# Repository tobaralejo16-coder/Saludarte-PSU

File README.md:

# Saludarte-PSU

### Sistema de asistencia y acompañamiento mediante aplicación Android y ESP32

**Saludarte_PSU** es un proyecto desarrollado en el contexto de PSU, que integra una aplicación móvil Android, un sistema embebido basado en ESP32 y un diseño de hardware electrónico para implementar funciones de asistencia, recordatorios y comunicación entre dispositivos.

El repositorio reúne el código fuente, los recursos multimedia y los archivos de diseño electrónico utilizados durante el desarrollo, montaje y pruebas del sistema.

## 1. Descripción del proyecto

Saludarte busca integrar herramientas de software y hardware en una solución tecnológica de apoyo a las actividades cotidianas.

El sistema integra:

- Una aplicación móvil Android para la interacción con el usuario.
- Un dispositivo basado en ESP32 para ejecutar las funciones del sistema embebido.
- Comunicación inalámbrica Bluetooth Low Energy (BLE) entre la aplicación y la ESP32.
- Recursos de audio para recordatorios, actividades y notificaciones.
- Hardware electrónico utilizado como referencia para el montaje, las conexiones y la soldadura de los componentes físicos del sistema.

## 2. Estructura del repositorio

```text
Saludarte-PSU/
│
├── App-Android/
│   └── Código fuente y recursos de la aplicación
│
├── Esp32/
│   └── Firmware, audios y configuración de ESP32
│
├── Hardware/
│   └── ESP32_Audio_3SPK/
│       ├── ESP32_Audio_3SPK.kicad_pro
│       ├── ESP32_Audio_3SPK.kicad_sch
│       ├── ESP32_Audio_3SPK.kicad_pcb
│       ├── Proyecto_Audio.pretty/
│       ├── models/
│       ├── vista/
│       └── Archivos complementarios
│
├── .gitignore
└── README.md
```

## 3. Aplicación Android

La aplicación está desarrollada en **Kotlin**, utilizando Android Studio.

Incluye componentes para la interfaz de usuario, la gestión de la comunicación Bluetooth BLE y recursos multimedia asociados con las funcionalidades del sistema.

**Contenido disponible:**

- Código fuente Kotlin.
- Interfaz y recursos gráficos.
- Archivos de audio MP3.
- Configuración de Gradle.
- Archivos necesarios para abrir y continuar desarrollando el proyecto en Android Studio.

**Ubicación:** `App-Android/`

### Apertura del proyecto

1. Descargar o clonar el repositorio.
2. Abrir Android Studio.
3. Seleccionar **Open**.
4. Buscar la carpeta `App-Android/`.
5. Esperar a que Gradle sincronice las dependencias.
6. Seleccionar un dispositivo Android compatible para ejecutar la aplicación.

## 4. Sistema ESP32

El firmware de la ESP32 implementa las funciones del sistema embebido y su comunicación con la aplicación móvil.

El proyecto incluye archivos relacionados con:

- Comunicación Bluetooth Low Energy (BLE).
- Reproducción y gestión de audio.
- Configuración de PlatformIO.
- Herramientas de diagnóstico.
- Pruebas y documentación técnica.

**Ubicación:** `Esp32/`

### Apertura del proyecto

1. Instalar Visual Studio Code.
2. Instalar la extensión PlatformIO.
3. Abrir la carpeta `Esp32/`.
4. Seleccionar la configuración correspondiente del proyecto.
5. Compilar el firmware y cargarlo en una ESP32 compatible.

Para información adicional, consultar el README incluido dentro de la carpeta del firmware.

## 5. Diseño y montaje de hardware

El hardware de Saludarte fue desarrollado utilizando **KiCad 10**, con el objetivo de organizar las conexiones electrónicas, definir los componentes del dispositivo y disponer de una referencia técnica para su implementación física.

Los archivos de diseño se utilizaron como apoyo durante el proceso de **montaje, conexión y soldadura de los componentes electrónicos** del sistema.

El proyecto incluye el esquemático electrónico, el diseño de PCB, bibliotecas de componentes, modelos tridimensionales y archivos complementarios de verificación.

### 5.1. Esquemático electrónico

El archivo `ESP32_Audio_3SPK.kicad_sch` contiene la representación de las conexiones eléctricas del sistema.

Permite consultar los componentes, las señales y la organización de los circuitos utilizados como referencia para el montaje físico.

### 5.2. Diseño de PCB

El archivo `ESP32_Audio_3SPK.kicad_pcb` contiene el diseño de la tarjeta electrónica, incluyendo la distribución de componentes y las conexiones entre ellos.

Este diseño forma parte de la documentación técnica utilizada durante el desarrollo e implementación del hardware.

### 5.3. Modelos tridimensionales

La carpeta `models/` contiene recursos tridimensionales asociados con el diseño electrónico.

Estos archivos permiten complementar la representación física de los componentes dentro del entorno de KiCad.

### 5.4. Bibliotecas y archivos complementarios

El proyecto también incluye:

- `Proyecto_Audio.pretty/`: biblioteca de huellas de componentes.
- `BOM_preliminar.csv`: lista preliminar de materiales.
- `ERC.json` y `DRC.json`: archivos relacionados con las verificaciones eléctricas y de diseño.
- `MONTAJE.md`: información relacionada con el montaje.
- `VALIDACION.md`: documentación de validación.
- `ESTADO_TRABAJO.md`: registro del estado del desarrollo.
- `LEEME.md`: información complementaria del proyecto.

### Apertura del proyecto de hardware

1. Instalar KiCad 10.
2. Descargar o clonar el repositorio.
3. Abrir la carpeta `Hardware/ESP32_Audio_3SPK/`.
4. Ejecutar el archivo `ESP32_Audio_3SPK.kicad_pro`.
5. Desde KiCad, abrir el editor de esquemáticos o el editor de PCB según corresponda.

Se recomienda conservar la estructura de carpetas original para mantener las referencias a bibliotecas, huellas y modelos tridimensionales.

**Ubicación:** `Hardware/ESP32_Audio_3SPK/`

## 6. Descarga del proyecto

El repositorio es público y puede consultarse sin necesidad de solicitar acceso.

Para descargar los archivos:

1. Abrir el repositorio Saludarte-PSU en GitHub.
2. Seleccionar el botón **Code**.
3. Elegir **Download ZIP**.
4. Extraer el archivo descargado.
5. Abrir el componente del proyecto que se desea consultar o modificar.

También puede clonarse mediante Git:

```bash
git clone https://github.com/tobaralejo16-coder/Saludarte-PSU.git
```

## 7. Estado del proyecto

| Componente | Estado |
|---|---|
| Aplicación Android | Código fuente disponible |
| Firmware ESP32 | Código fuente disponible |
| Comunicación Bluetooth BLE | Implementada en el código |
| Esquemático electrónico | Disponible |
| Diseño PCB | Disponible |
| Modelos 3D | Archivos disponibles |
| Montaje y soldadura | Realizados utilizando el diseño de hardware como referencia |
| Documentación técnica | Incluida en las carpetas correspondientes |

La disponibilidad de los archivos de diseño permite consultar y continuar desarrollando el sistema. Para realizar nuevas fabricaciones o modificaciones de hardware, se recomienda revisar previamente los documentos de validación y verificar las conexiones y componentes.

## 8. Desarrollo y colaboración

Saludarte-PSU es un repositorio destinado a centralizar los diferentes componentes del proyecto y facilitar su consulta, mantenimiento y desarrollo.

El código fuente y los archivos publicados pueden consultarse y descargarse públicamente.

Las personas interesadas en colaborar pueden proponer mejoras mediante los mecanismos de contribución disponibles en GitHub.

---

**Proyecto Saludarte — PSU**

Repositorio mantenido en GitHub: [Saludarte-PSU](https://github.com/tobaralejo16-coder/Saludarte-PSU).

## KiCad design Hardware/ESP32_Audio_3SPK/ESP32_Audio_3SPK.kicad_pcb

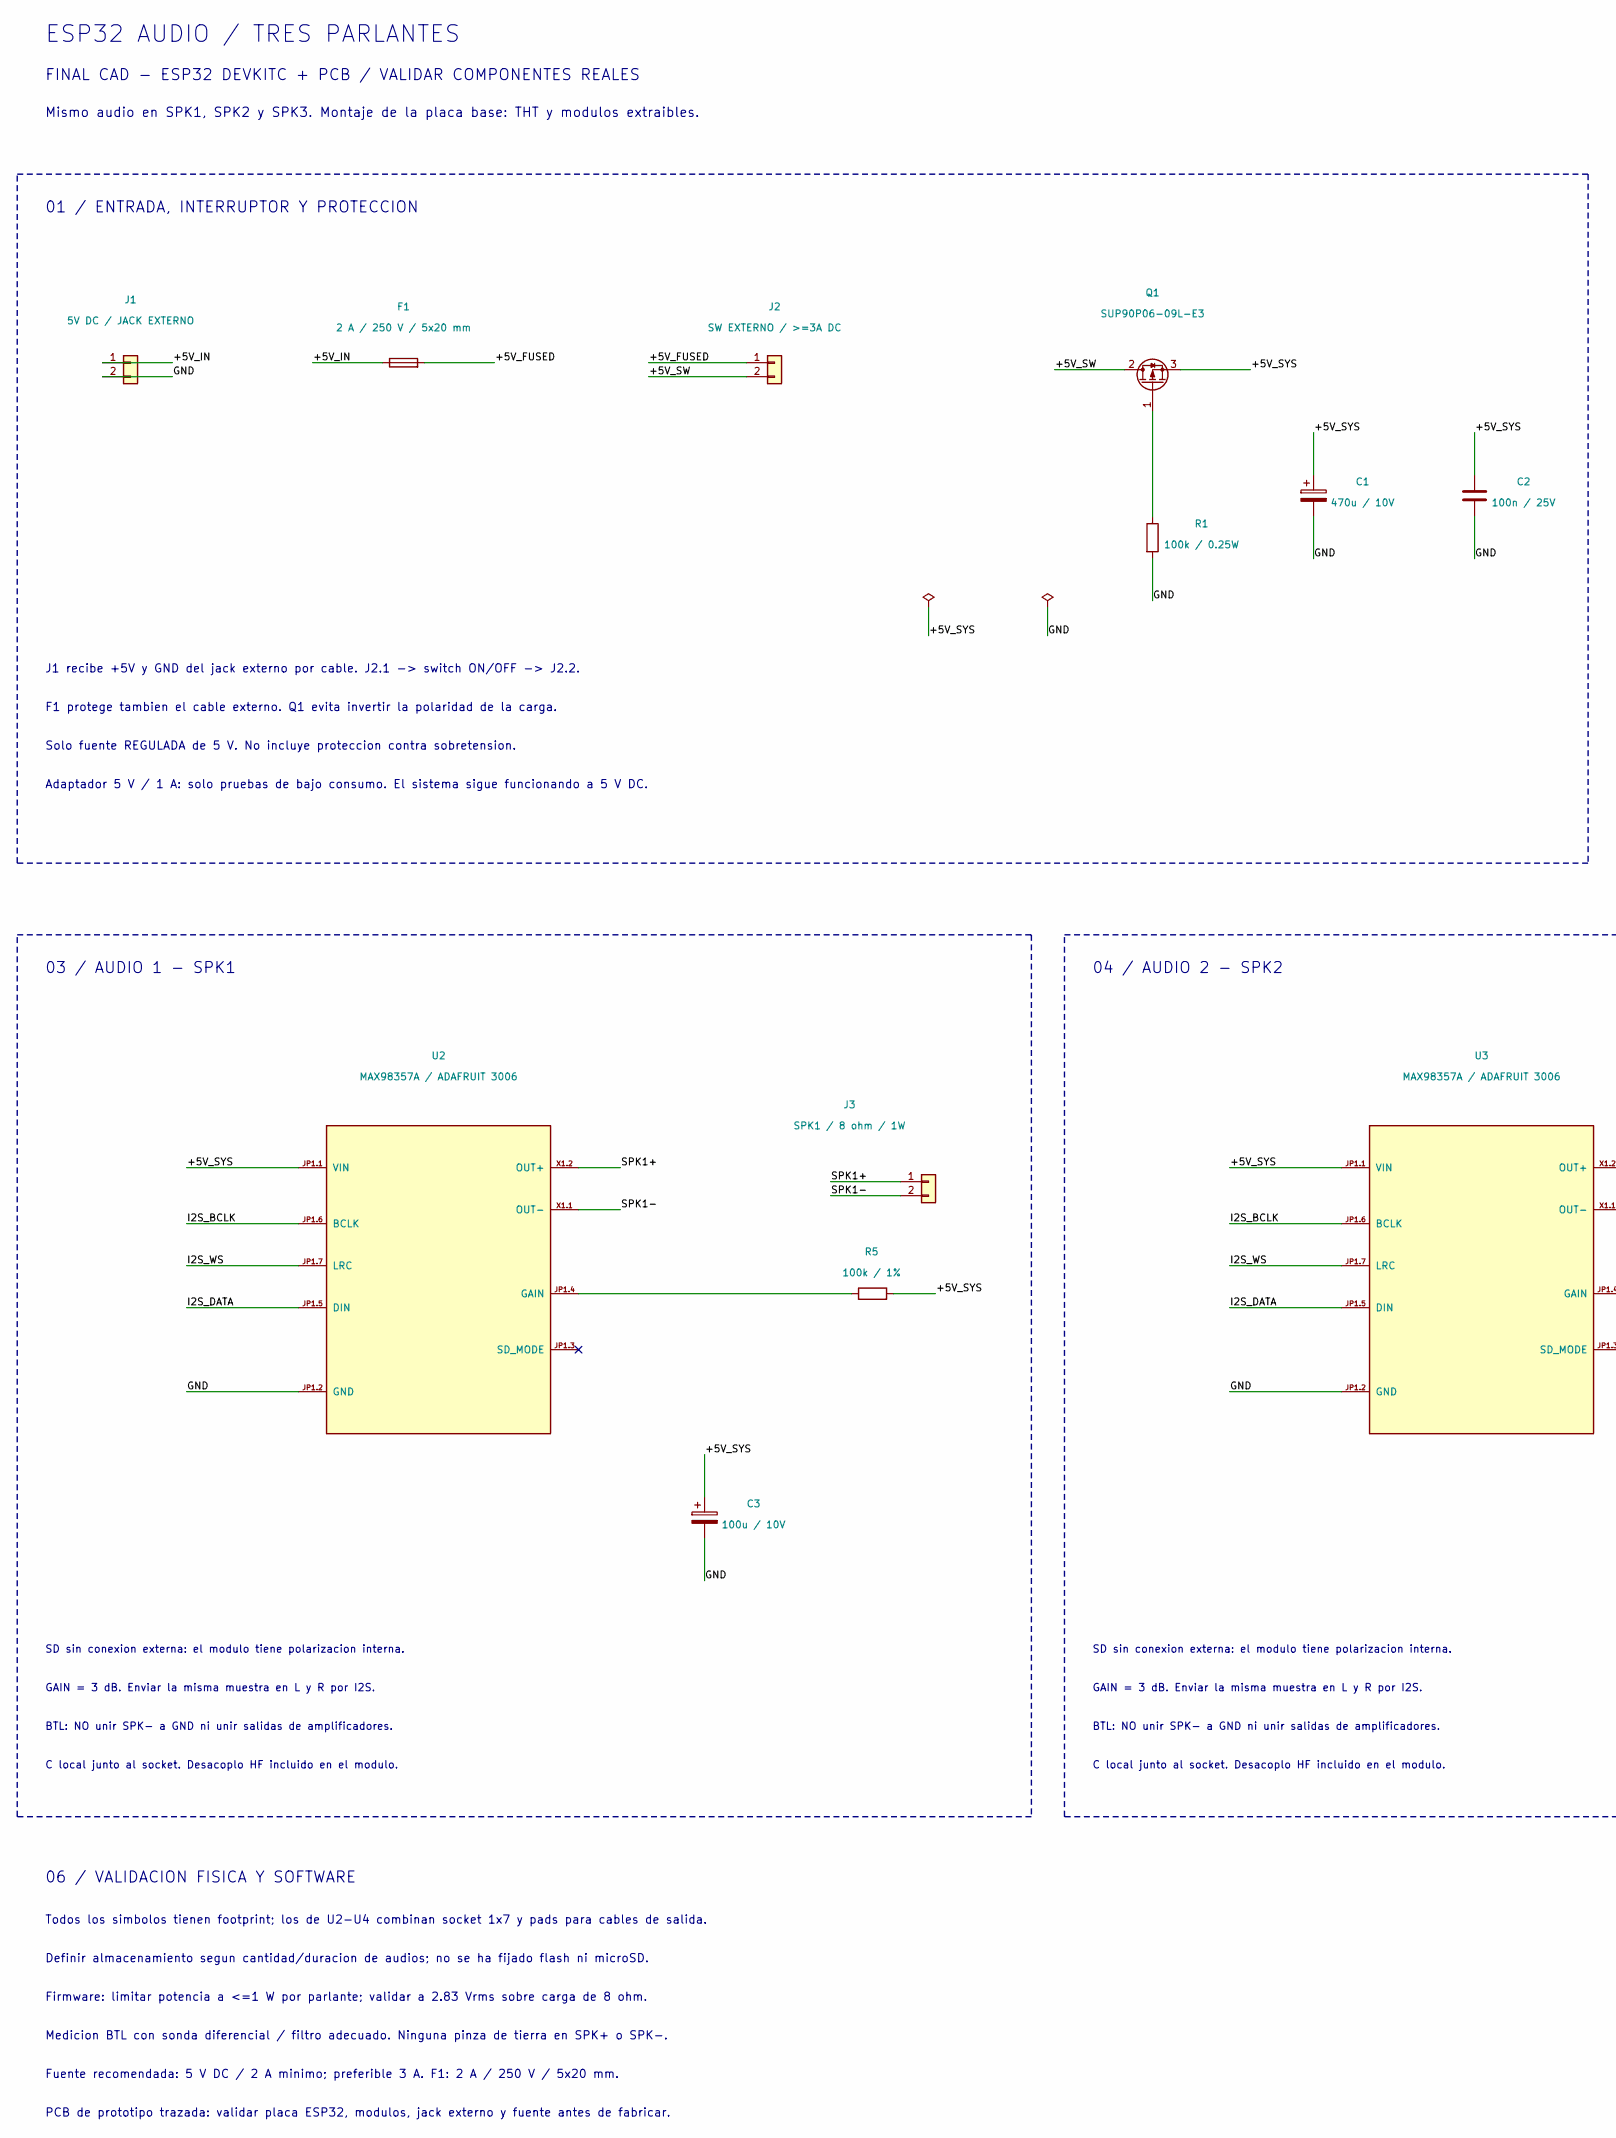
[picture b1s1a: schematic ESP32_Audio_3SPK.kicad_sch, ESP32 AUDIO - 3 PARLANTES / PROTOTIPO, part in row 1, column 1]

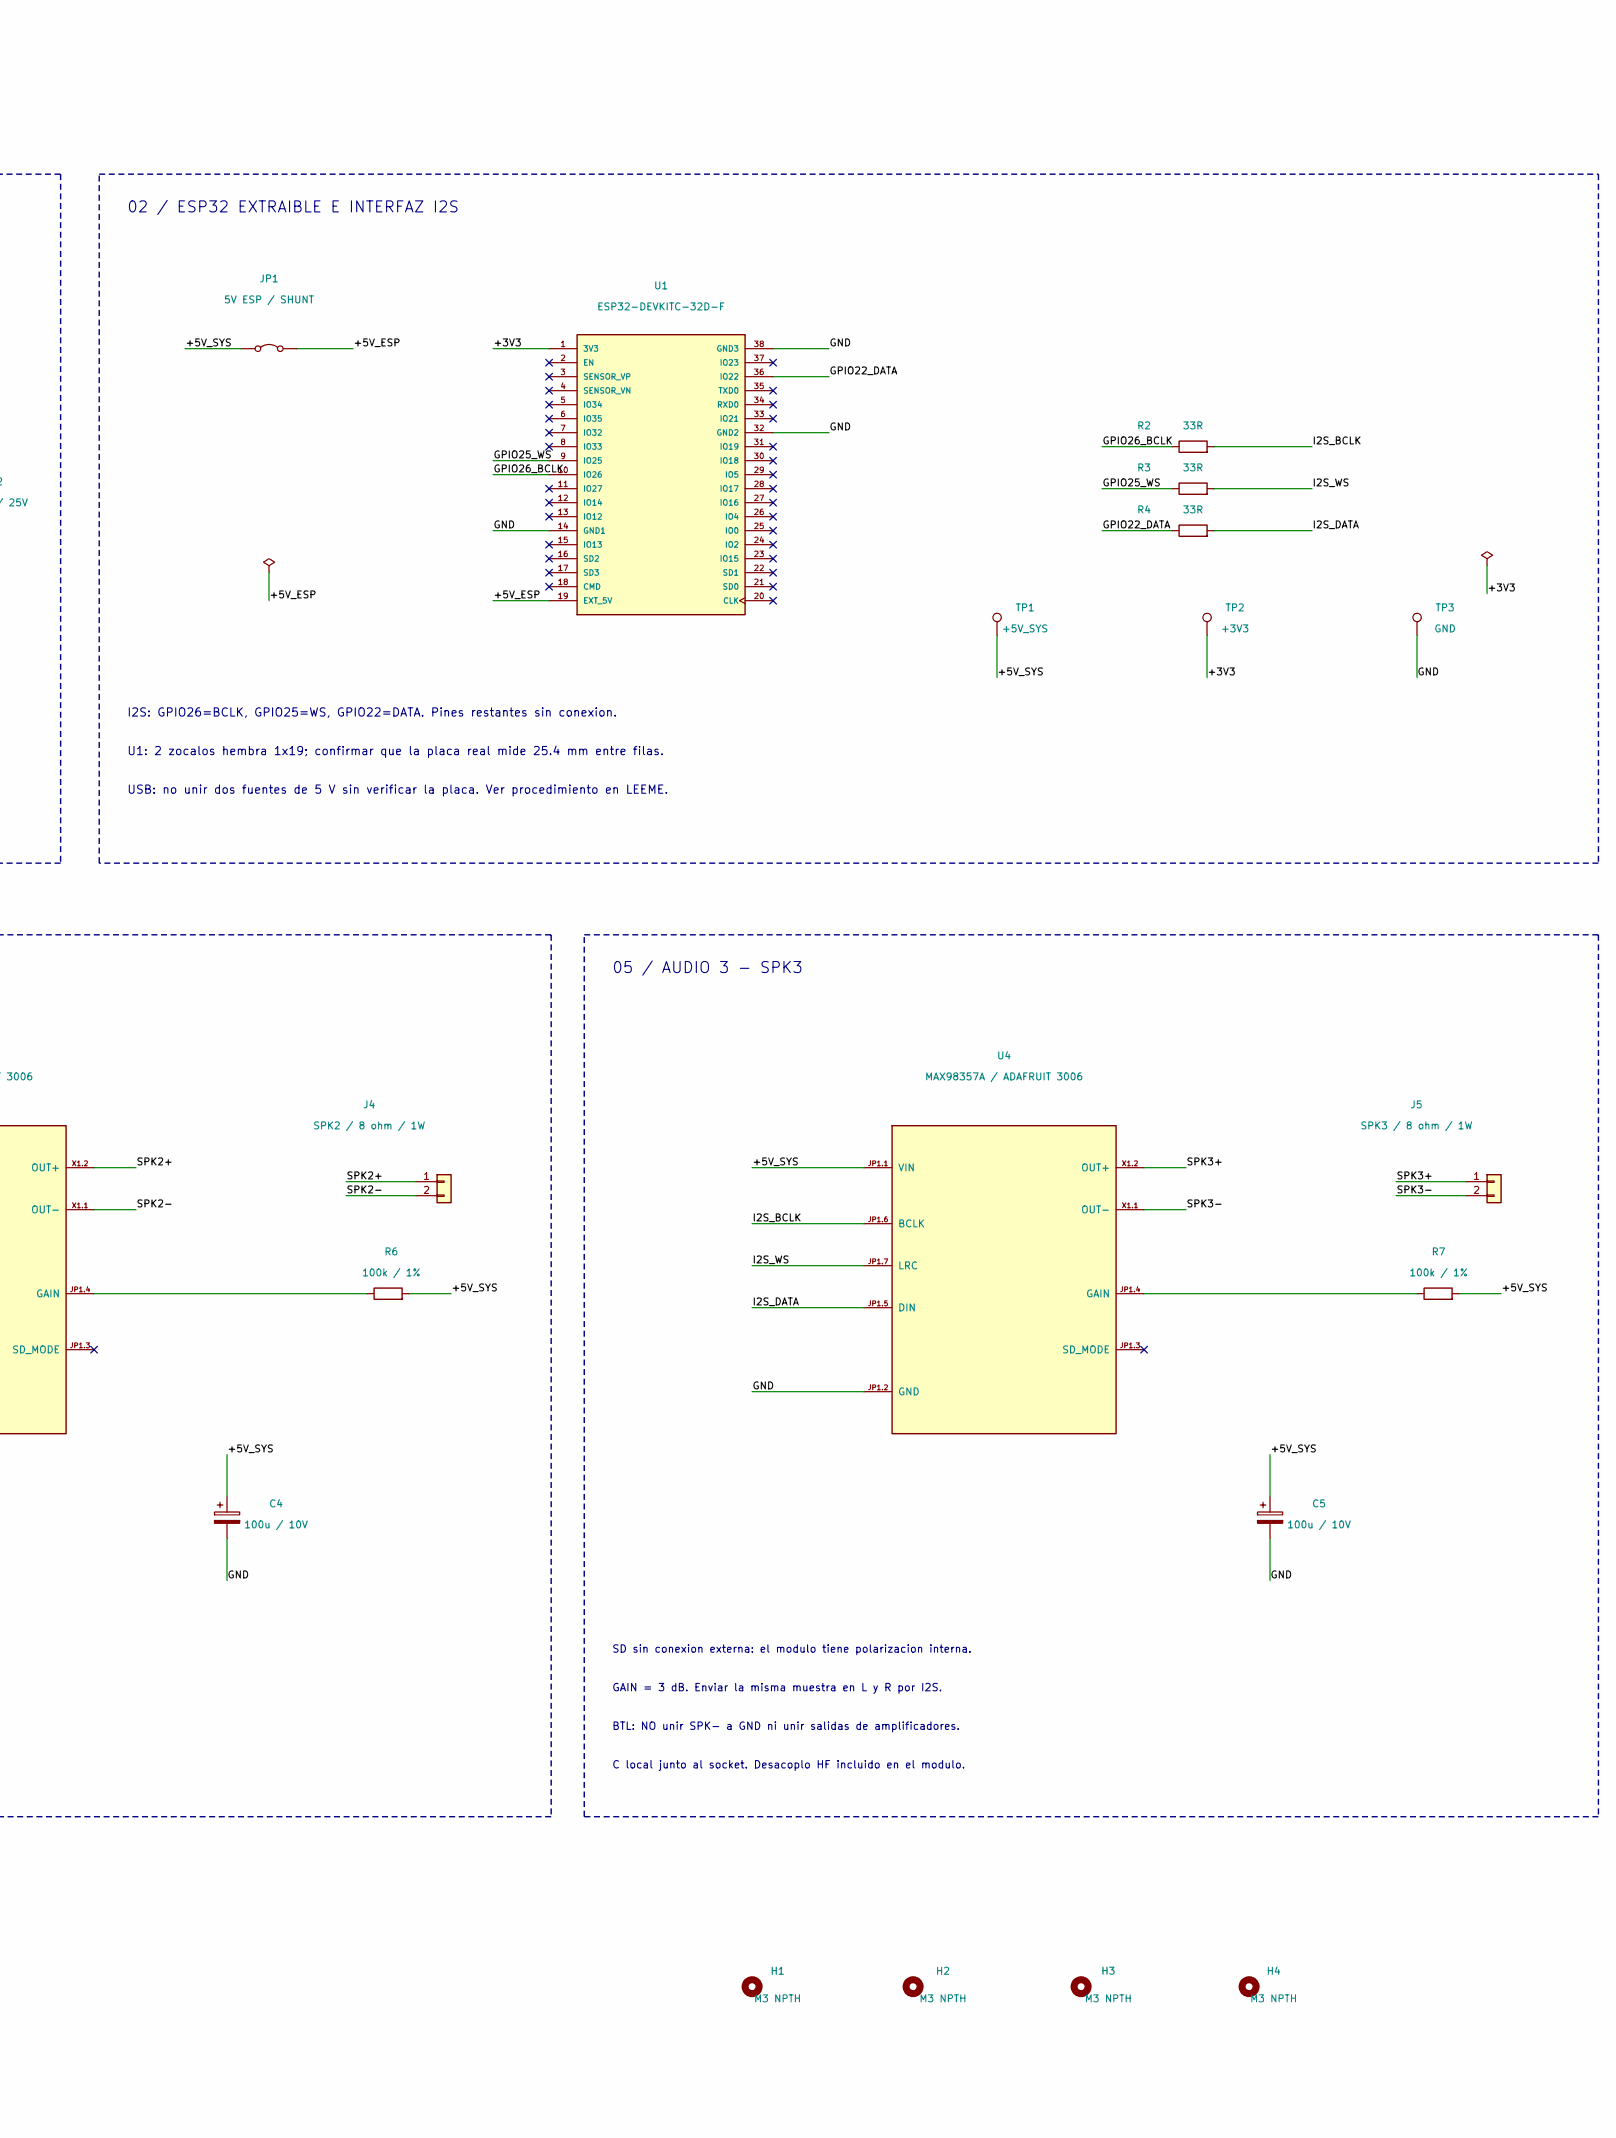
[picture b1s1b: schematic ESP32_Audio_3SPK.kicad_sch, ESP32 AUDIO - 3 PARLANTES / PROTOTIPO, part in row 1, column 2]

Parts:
C1: 470u / 10V; CP_Radial_D8.0mm_P3.50mm
C2: 100n / 25V; C_Disc_D5.0mm_W2.5mm_P2.50mm
C3, C4, C5: 100u / 10V; CP_Radial_D5.0mm_P2.00mm
F1: 2 A / 250 V / 5x20 mm; Fuseholder_Cylinder-5x20mm_Schurter_0031_8201_Horizontal_Op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
H1, H2, H3, H4: M3 NPTH; MountingHole_3.2mm_M3
J1: 5V DC / JACK EXTERNO; TerminalBlock_Phoenix_MKDS-1,5-2-5.08_1x02_P5.08mm_Horizont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
J2: SW EXTERNO / >=3A DC; TerminalBlock_Phoenix_MKDS-1,5-2-5.08_1x02_P5.08mm_Horizont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
J3: SPK1 / 8 ohm / 1W; TerminalBlock_Phoenix_MKDS-1,5-2-5.08_1x02_P5.08mm_Horizont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
J4: SPK2 / 8 ohm / 1W; TerminalBlock_Phoenix_MKDS-1,5-2-5.08_1x02_P5.08mm_Horizont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
J5: SPK3 / 8 ohm / 1W; TerminalBlock_Phoenix_MKDS-1,5-2-5.08_1x02_P5.08mm_Horizont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
JP1: 5V ESP / SHUNT; PinHeader_1x02_P2.54mm_Vertical
Q1: SUP90P06-09L-E3; TO-220-3_Vertical
R1: 100k / 0.25W; R_Axial_DIN0309_L9.0mm_D3.2mm_P5.08mm_Vertical
R2, R3, R4: 33R; R_Axial_DIN0207_L6.3mm_D2.5mm_P7.62mm_Horizontal
R5, R6, R7: 100k / 1%; R_Axial_DIN0207_L6.3mm_D2.5mm_P7.62mm_Horizontal
TP1: +5V_SYS; TestPoint_THTPad_D2.0mm_Drill1.0mm
TP2: +3V3; TestPoint_THTPad_D2.0mm_Drill1.0mm
TP3: GND; TestPoint_THTPad_D2.0mm_Drill1.0mm
U1: ESP32-DEVKITC-32D-F; MODULE_ESP32-DEVKITC
U2, U3, U4: MAX98357A / ADAFRUIT 3006; AMP_3006_DOCK_1x07_2WIRE

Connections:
/+3V3: TP2.1, U1.1 (3V3)
/+5V_ESP: JP1.2 (B), U1.19 (EXT_5V)
/+5V_FUSED: F1.2, J2.1
/+5V_IN: F1.1, J1.1
/+5V_SW: J2.2, Q1.2 (D)
/+5V_SYS: C1.1, C2.1, C3.1, C4.1, C5.1, JP1.1 (A), Q1.3 (S), R5.2, R6.2, R7.2, TP1.1, U2.JP1.1 (VIN), U3.JP1.1 (VIN), U4.JP1.1 (VIN)
/GND: C1.2, C2.2, C3.2, C4.2, C5.2, J1.2, R1.2, TP3.1, U1.14 (GND1), U1.32 (GND2), U1.38 (GND3), U2.JP1.2 (GND), U3.JP1.2 (GND), U4.JP1.2 (GND)
/GPIO22_DATA: R4.1, U1.36 (IO22)
/GPIO25_WS: R3.1, U1.9 (IO25)
/GPIO26_BCLK: R2.1, U1.10 (IO26)
/I2S_BCLK: R2.2, U2.JP1.6 (BCLK), U3.JP1.6 (BCLK), U4.JP1.6 (BCLK)
/I2S_DATA: R4.2, U2.JP1.5 (DIN), U3.JP1.5 (DIN), U4.JP1.5 (DIN)
/I2S_WS: R3.2, U2.JP1.7 (LRC), U3.JP1.7 (LRC), U4.JP1.7 (LRC)
/SPK1+: J3.1, U2.X1.2 (OUT+)
/SPK1-: J3.2, U2.X1.1 (OUT-)
/SPK2+: J4.1, U3.X1.2 (OUT+)
/SPK2-: J4.2, U3.X1.1 (OUT-)
/SPK3+: J5.1, U4.X1.2 (OUT+)
/SPK3-: J5.2, U4.X1.1 (OUT-)
unnamed: Q1.1 (G), R1.1
unnamed: R5.1, U2.JP1.4 (GAIN)
unnamed: R6.1, U3.JP1.4 (GAIN)
unnamed: R7.1, U4.JP1.4 (GAIN)

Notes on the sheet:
C local junto al socket. Desacoplo HF incluido en el modulo.
J1 recibe +5V y GND del jack externo por cable. J2.1 -> switch ON/OFF -> J2.2.
Medicion BTL con sonda diferencial / filtro adecuado. Ninguna pinza de tierra en SPK+ o SPK-.
01 / ENTRADA, INTERRUPTOR Y PROTECCION
GAIN = 3 dB. Enviar la misma muestra en L y R por I2S.
USB: no unir dos fuentes de 5 V sin verificar la placa. Ver procedimiento en LEEME.
04 / AUDIO 2 - SPK2
BTL: NO unir SPK- a GND ni unir salidas de amplificadores.
02 / ESP32 EXTRAIBLE E INTERFAZ I2S
SD sin conexion externa: el modulo tiene polarizacion interna.
05 / AUDIO 3 - SPK3
F1 protege tambien el cable externo. Q1 evita invertir la polaridad de la carga.
FINAL CAD - ESP32 DEVKITC + PCB / VALIDAR COMPONENTES REALES
Fuente recomendada: 5 V DC / 2 A minimo; preferible 3 A. F1: 2 A / 250 V / 5x20 mm.
PCB de prototipo trazada: validar placa ESP32, modulos, jack externo y fuente antes de fabricar.
Adaptador 5 V / 1 A: solo pruebas de bajo consumo. El sistema sigue funcionando a 5 V DC.
06 / VALIDACION FISICA Y SOFTWARE
Definir almacenamiento segun cantidad/duracion de audios; no se ha fijado flash ni microSD.
Mismo audio en SPK1, SPK2 y SPK3. Montaje de la placa base: THT y modulos extraibles.
Firmware: limitar potencia a <=1 W por parlante; validar a 2.83 Vrms sobre carga de 8 ohm.
Todos los simbolos tienen footprint; los de U2-U4 combinan socket 1x7 y pads para cables de salida.
03 / AUDIO 1 - SPK1
I2S: GPIO26=BCLK, GPIO25=WS, GPIO22=DATA. Pines restantes sin conexion.
Solo fuente REGULADA de 5 V. No incluye proteccion contra sobretension.
U1: 2 zocalos hembra 1x19; confirmar que la placa real mide 25.4 mm entre filas.
ESP32 AUDIO / TRES PARLANTES

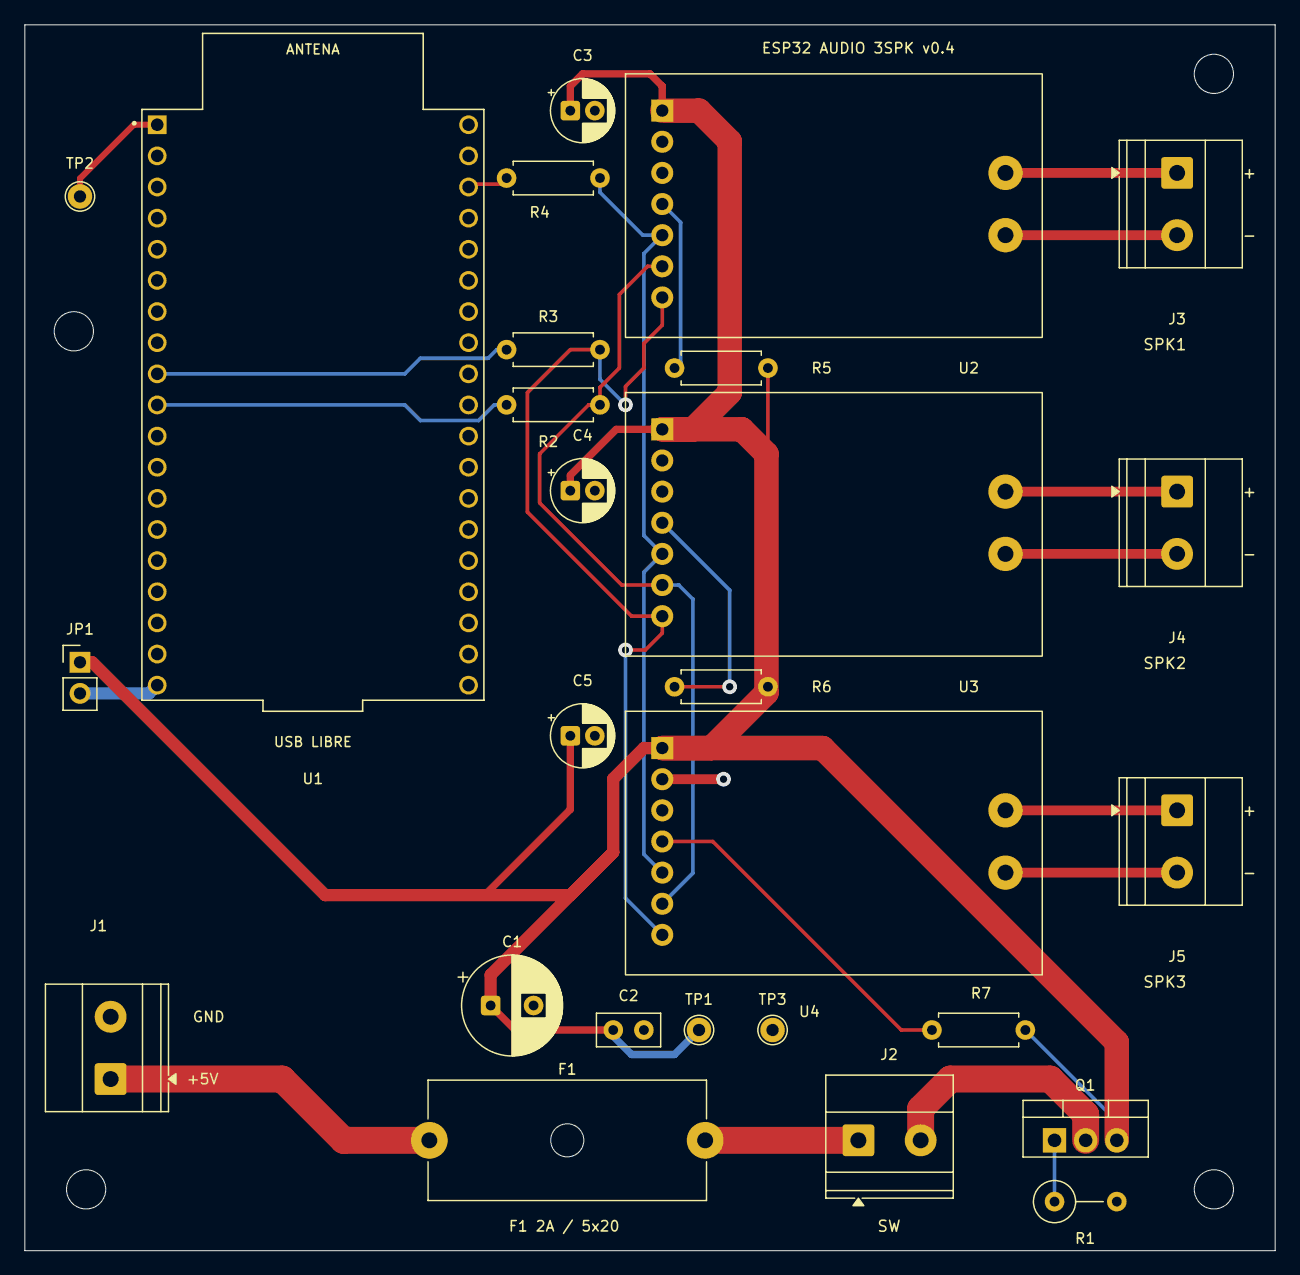
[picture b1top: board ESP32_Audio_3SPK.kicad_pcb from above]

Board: 2 copper layers, 102.0 x 100.0 mm, 31 parts (0 on the bottom side), 23 nets.
